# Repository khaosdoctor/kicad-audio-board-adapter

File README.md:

# Twilight Adapter

KiCad project for a 9V-powered audio effects adapter board: input/output audio
jacks, a true-bypass DPDT switch, two DIP switches, a trim potentiometer, an
LED indicator, test points, and header connectors for interfacing with
another board.

> This design is not mine. It was designed by **Akim Kimliuk**, who gave
> permission to use it here since he isn't able to sell it outside his
> country. All credit for the original design goes to him.

## PCB preview

| Top | Bottom |
|-----|--------|
|  |  |

## Hardware overview

Interactive BOM: [khaosdoctor.github.io/kicad-audio-board-adapter/bom/ibom.html](https://khaosdoctor.github.io/kicad-audio-board-adapter/bom/ibom.html)

| Ref        | Part                  | Function                          |
|------------|-----------------------|------------------------------------|
| J1/J2      | Audio jack (switched) | Input / output                     |
| J5         | Barrel jack + switch  | 9V power input                     |
| SW1        | DPDT switch           | True-bypass footswitch             |
| SW2/SW3    | DIP switch            | Mode/routing selection             |
| RV1        | Trim potentiometer    | Calibration                        |
| D1         | LED                   | Status indicator                   |
| D2         | 1N4001 diode          | Reverse-polarity protection        |
| C1/C2      | 47uF electrolytic     | Power filtering                    |
| R1         | 10k resistor          | Bias/pull                          |
| TP1-TP5    | Test points           | Debug/calibration probing          |
| J3/J4/J8   | 2-pin headers         | Board-to-board connections         |
| J6/J7      | 2x5 headers           | Board-to-board connections         |

The board is a 2-layer PCB designed in KiCad 10.

## Generating manufacturing files with KiBot

This project uses [KiBot](https://github.com/INTI-CMNB/KiBot) to generate
gerbers, drill files, pick & place, BOM, documentation and 3D outputs
straight from the KiCad source files, via `kibot.yaml`.

### Outputs produced

| Group           | Outputs                                                        | Directory              |
|-----------------|------------------------------------------------------------------|-------------------------|
| `fabrication`   | Gerbers, Excellon drill files                                    | `Manufacturing/Gerbers` |
| `assembly`      | Pick & place position file, BOM (CSV)                            | `Manufacturing/Assembly`|
| `documentation` | Schematic PDF, PCB PDF, interactive HTML BOM                      | `Documentation`, `bom`  |
| `3d`            | STEP model, top/bottom 3D renders                                 | `3D`                    |

A zipped bundle of gerbers + drill files ready to send to a fab house is also
produced under `Manufacturing/manufacturing_zip.zip`. A JLCPCB-specific BOM
(`bom_jlcpcb`) filtered to parts with an LCSC part number is available but not
run by default.

### Running locally

Install KiCad (10.x) and KiBot, then from the repository root run:

```bash
pip install kibot
kibot -e Twilight_Adapter.kicad_sch -b Twilight_Adapter.kicad_pcb
```

To generate a single group or output, pass its name as a target, e.g.:

```bash
kibot -e Twilight_Adapter.kicad_sch -b Twilight_Adapter.kicad_pcb fabrication
```

### Running with Docker

No local KiCad/KiBot install is required if you have Docker:

```bash
docker run --rm -v "$(pwd)":/mnt ghcr.io/inti-cmnb/kicad10_auto_full:latest \
  kibot -e Twilight_Adapter.kicad_sch -b Twilight_Adapter.kicad_pcb
```

### Running in CI

The [`kibot.yml`](.github/workflows/kibot.yml) workflow runs KiBot on every
push and pull request and uploads the generated files as a build artifact.
On pushes to `main` it also commits the refreshed `bom/ibom.html`,
`3D/render_top.png` and `3D/render_bottom.png` back to the repo, which is
what keeps the PCB preview and interactive BOM link above up to date.

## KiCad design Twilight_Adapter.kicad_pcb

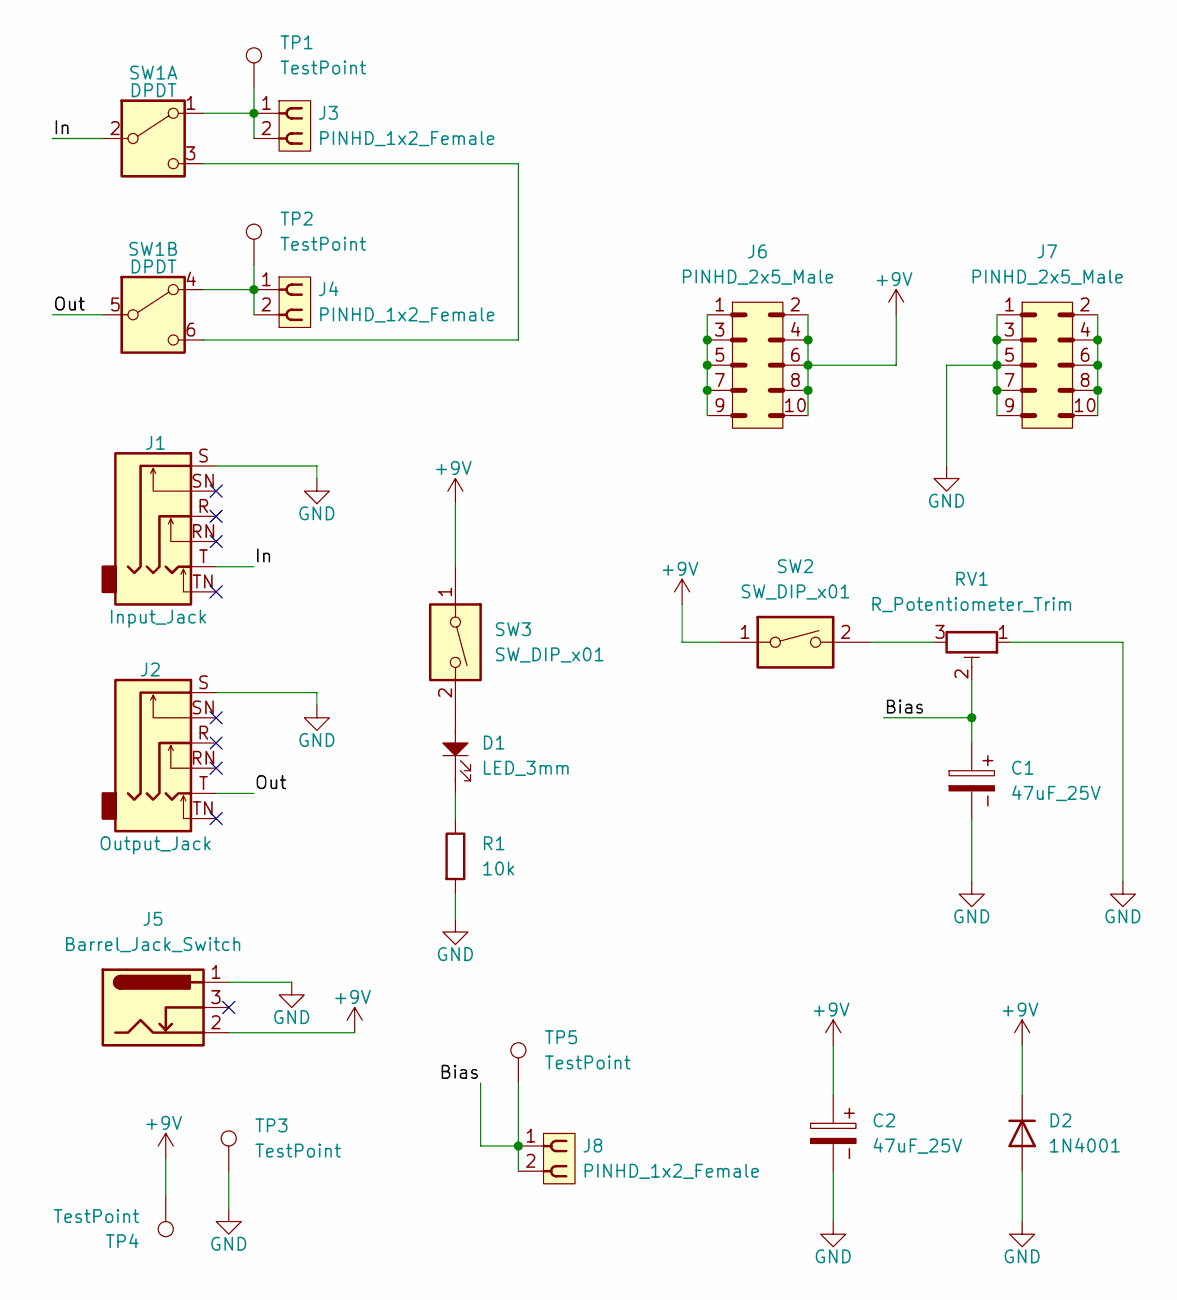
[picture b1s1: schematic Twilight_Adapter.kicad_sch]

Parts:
C1, C2: 47uF_25V; CP_Radial_D6.3mm_P2.50mm
D1: LED_3mm; LED_D3.0mm
D2: 1N4001; D_DO-41_SOD81_P10.16mm_Horizontal
J1: Input_Jack; Jack_6.35mm_Neutrik_NMJ6HCD2_Horizontal
J2: Output_Jack; Jack_6.35mm_Neutrik_NMJ6HCD2_Horizontal
J3, J4, J8: PINHD_1x2_Female; PinSocket_1x02_P2.54mm_Vertical
J5: Barrel_Jack_Switch; BarrelJack_GCT_DCJ200-10-A_Horizontal
J6, J7: PINHD_2x5_Male; PinHeader_2x05_P2.54mm_Vertical
R1: 10k; R_Axial_DIN0207_L6.3mm_D2.5mm_P10.16mm_Horizontal
RV1: R_Potentiometer_Trim; Potentiometer_Bourns_3296W_Vertical
SW1: DPDT; SW_5.8_5.8_DPDT
SW2, SW3: SW_DIP_x01; SW_DIP_SPSTx01_Slide_9.78x4.72mm_W7.62mm_P2.54mm
TP1, TP2, TP3, TP4, TP5: TestPoint; TestPoint_Loop_D2.54mm_Drill1.5mm_Beaded

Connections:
+9V: C2.1, D2.1 (K), J5.2, J6.2, J6.4, J6.6, J6.8, J6.10, SW2.1, SW3.1, TP4.1
/Bias: C1.1, J8.1, J8.2, RV1.2, TP5.1
/In: J1.T, SW1.2 (B)
/Out: J2.T, SW1.5 (B)
GND: C1.2, C2.2, D2.2 (A), J1.S, J2.S, J5.1, J7.1, J7.3, J7.5, J7.7, J7.9, R1.1, RV1.1, TP3.1
unnamed: D1.1, R1.2
unnamed: D1.2, SW3.2
unnamed: J6.1, J6.3, J6.5, J6.7, J6.9
unnamed: J7.2, J7.4, J7.6, J7.8, J7.10
unnamed: RV1.3, SW2.2
unnamed: J3.1, J3.2, SW1.1 (A), TP1.1
unnamed: SW1.3 (C), SW1.6 (C)
unnamed: J4.1, J4.2, SW1.4 (A), TP2.1

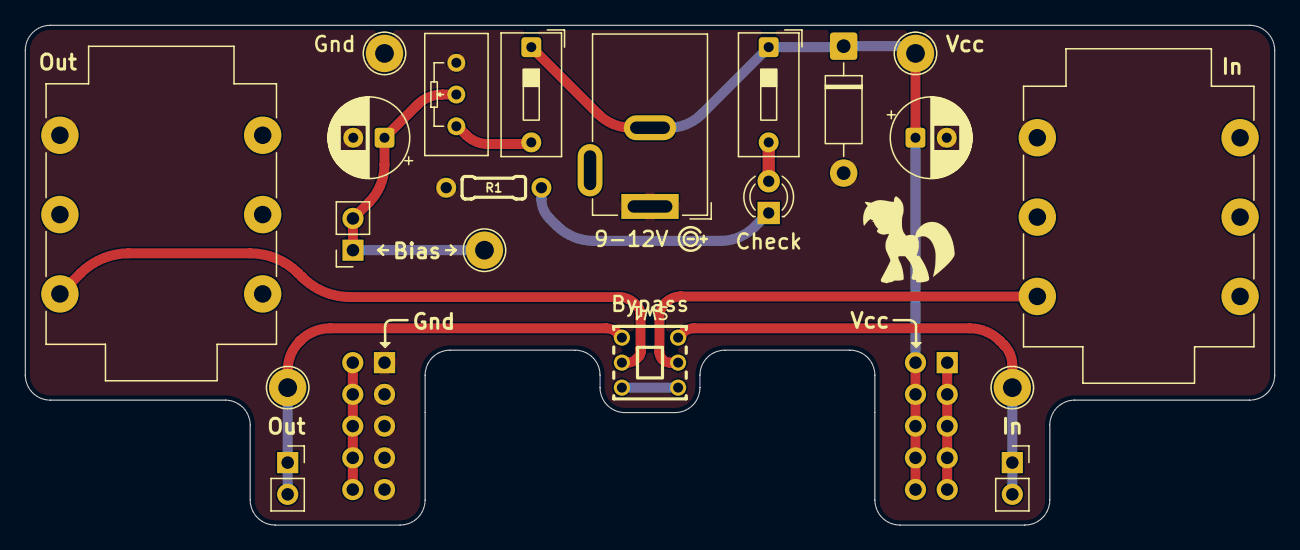
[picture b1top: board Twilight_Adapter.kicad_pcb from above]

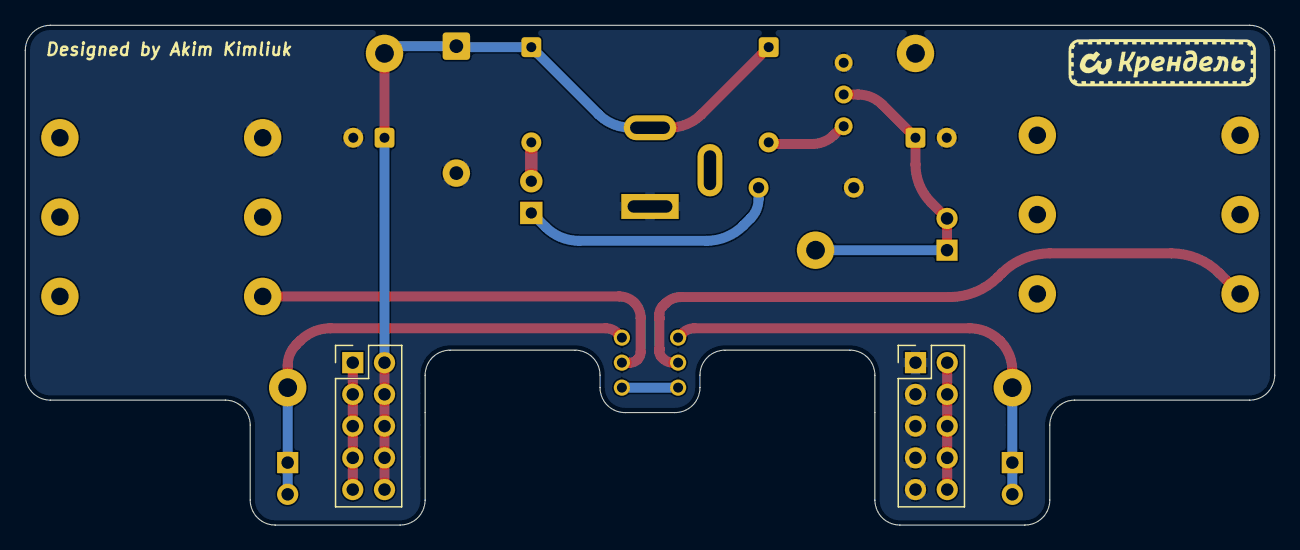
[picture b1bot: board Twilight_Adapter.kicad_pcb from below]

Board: 2 copper layers, 100.0 x 40.0 mm, 22 parts (2 on the bottom side), 13 nets.
